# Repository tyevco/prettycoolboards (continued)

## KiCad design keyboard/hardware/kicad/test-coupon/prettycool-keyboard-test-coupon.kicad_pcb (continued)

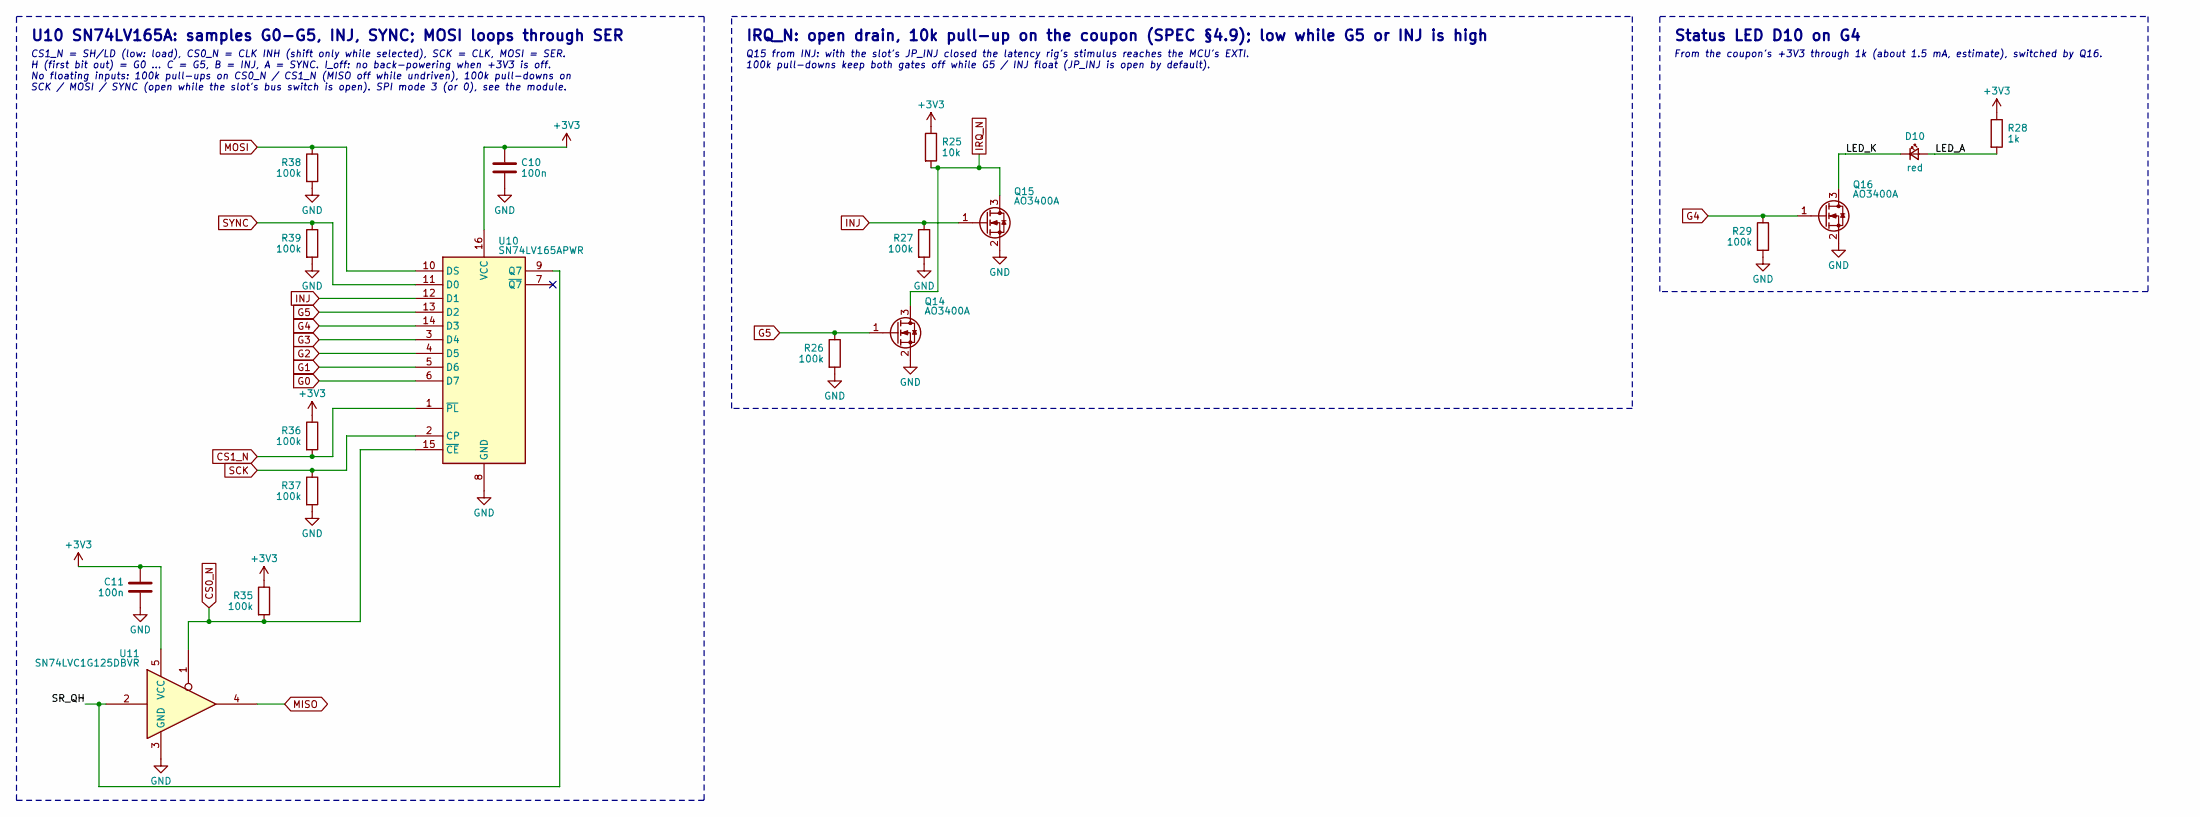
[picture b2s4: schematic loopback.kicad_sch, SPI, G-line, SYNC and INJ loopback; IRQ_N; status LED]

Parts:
C10, C11: 100n; C_0402_1005Metric; MPN CL05B104KO5NNNC; LCSC C1525
D10: red; LED_0603_1608Metric; MPN KT-0603R; LCSC C2286
Q14, Q15, Q16: AO3400A; SOT-23; MPN AO3400A; LCSC C20917
R25: 10k; R_0402_1005Metric; MPN 0402WGF1002TCE; LCSC C25744
R26, R27, R29, R35, R36, R37, R38, R39: 100k; R_0402_1005Metric; MPN 0402WGF1003TCE; LCSC C25741
R28: 1k; R_0402_1005Metric; MPN 0402WGF1001TCE; LCSC C11702
U10: SN74LV165APWR; TSSOP-16_4.4x5mm_P0.65mm; MPN SN74LV165APWR; LCSC C201716
U11: SN74LVC1G125DBVR; SOT-23-5; MPN SN74LVC1G125DBVR; LCSC C23654

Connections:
+3V3: C10.1, C11.1, R25.1, R28.1, R35.1, R36.1, U10.16 (VCC), U11.5 (VCC); also elsewhere on the board
/SPI, G-line, SYNC and INJ loopback; IRQ_N; status LED/LED_A: D10.2 (A), R28.2
/SPI, G-line, SYNC and INJ loopback; IRQ_N; status LED/LED_K: D10.1 (K), Q16.3 (D)
/SPI, G-line, SYNC and INJ loopback; IRQ_N; status LED/SR_QH: U10.9 (Q7), U11.2
CS0_N: R35.2, U10.15 (~CE), U11.1; also elsewhere on the board
CS1_N: R36.2, U10.1 (~PL); also elsewhere on the board
G0: U10.6 (D7); also elsewhere on the board
G1: U10.5 (D6); also elsewhere on the board
G2: U10.4 (D5); also elsewhere on the board
G3: U10.3 (D4); also elsewhere on the board
G4: Q16.1 (G), R29.1, U10.14 (D3); also elsewhere on the board
G5: Q14.1 (G), R26.1, U10.13 (D2); also elsewhere on the board
GND: C10.2, C11.2, Q14.2 (S), Q15.2 (S), Q16.2 (S), R26.2, R27.2, R29.2, R37.2, R38.2, R39.2, U10.8 (GND), U11.3 (GND); also elsewhere on the board
INJ: Q15.1 (G), R27.1, U10.12 (D1); also elsewhere on the board
IRQ_N: Q14.3 (D), Q15.3 (D), R25.2; also elsewhere on the board
MISO: U11.4; also elsewhere on the board
MOSI: R38.1, U10.10 (DS); also elsewhere on the board
SCK: R37.1, U10.2 (CP); also elsewhere on the board
SYNC: R39.1, U10.11 (D0); also elsewhere on the board

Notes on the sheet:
U10 SN74LV165A: samples G0-G5, INJ, SYNC; MOSI loops through SER
CS1_N = SH/LD (low: load), CS0_N = CLK INH (shift only while selected), SCK = CLK, MOSI = SER. H (first bit out) = G0 ... C = G5, B = INJ, A = SYNC. I_off: no back-powering when +3V3 is off. No floating inputs: 100k pull-ups on CS0_N / CS1_N (MISO off while undriven), 100k pull-downs on SCK / MOSI 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
IRQ_N: open drain, 10k pull-up on the coupon (SPEC §4.9); low while G5 or INJ is high
Q15 from INJ: with the slot's JP_INJ closed the latency rig's stimulus reaches the MCU's EXTI. 100k pull-downs keep both gates off while G5 / INJ float (JP_INJ is open by default).
Status LED D10 on G4
From the coupon's +3V3 through 1k (about 1.5 mA, estimate), switched by Q16.

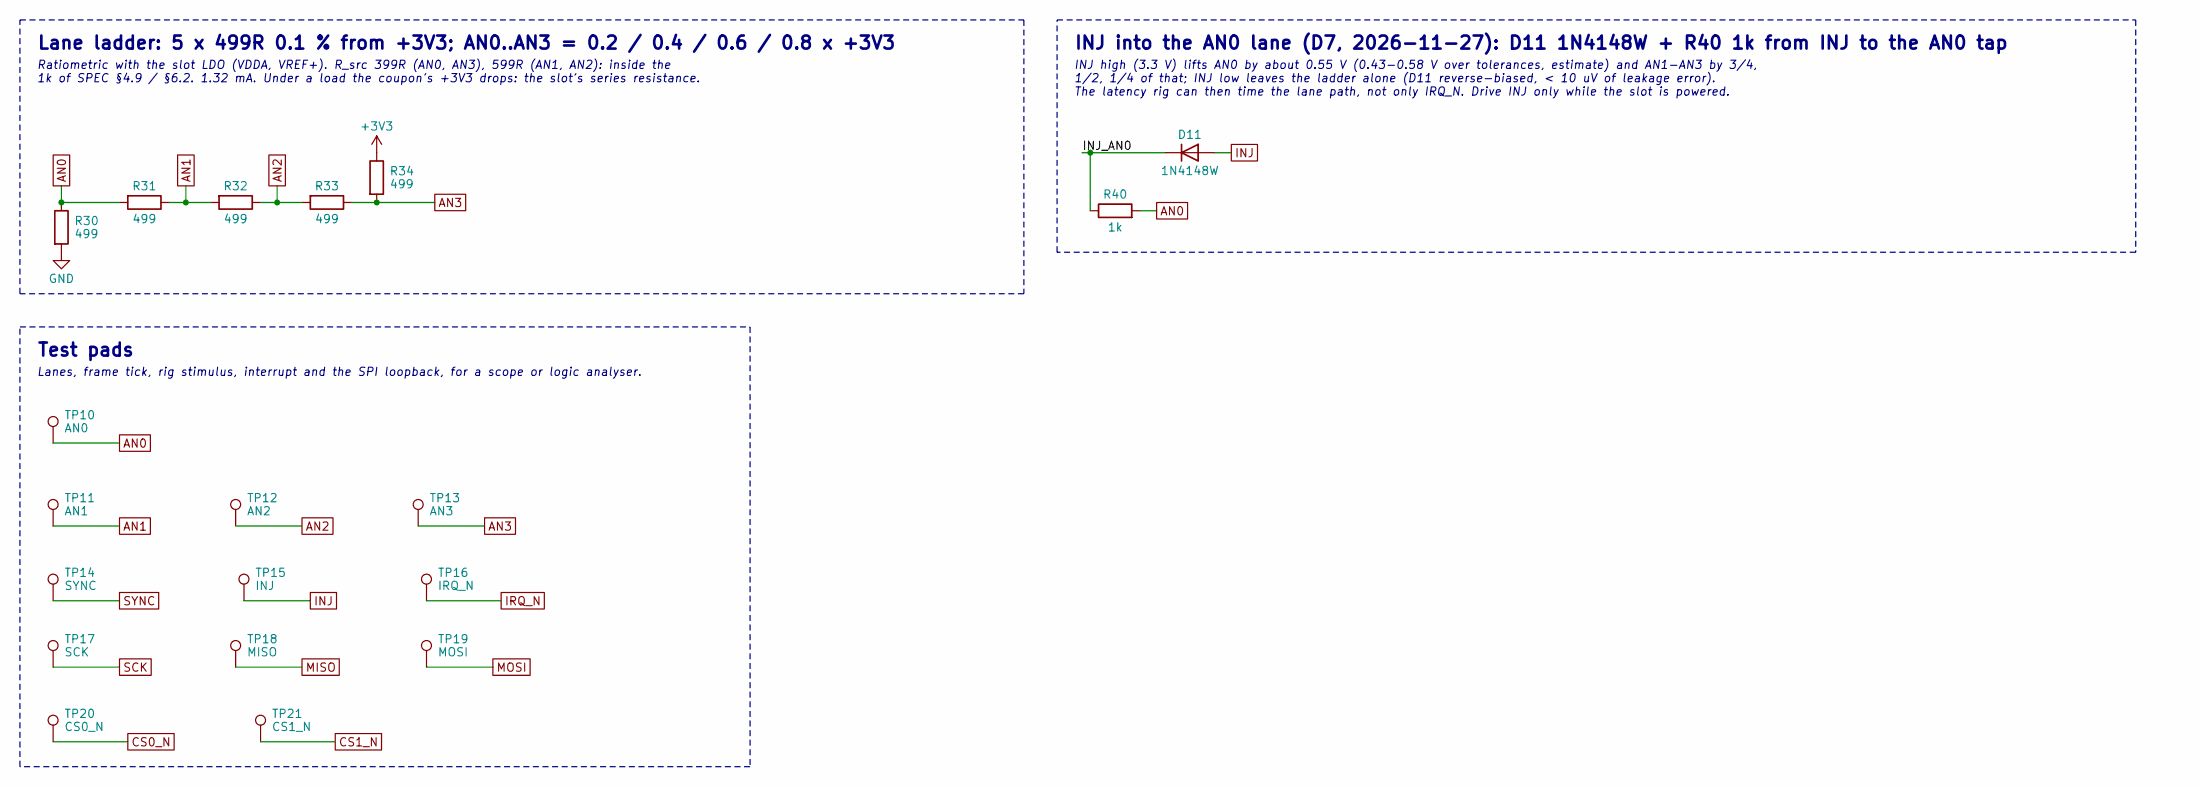
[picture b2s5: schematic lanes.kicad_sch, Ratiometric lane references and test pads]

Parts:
D11: 1N4148W; D_SOD-123; MPN 1N4148W; LCSC C81598
R30, R31, R32, R33, R34: 499; R_0603_1608Metric; MPN AR03BTCX4990; LCSC C2889161
R40: 1k; R_0402_1005Metric; MPN 0402WGF1001TCE; LCSC C11702
TP10: AN0; TestPoint_Pad_D1.0mm
TP11: AN1; TestPoint_Pad_D1.0mm
TP12: AN2; TestPoint_Pad_D1.0mm
TP13: AN3; TestPoint_Pad_D1.0mm
TP14: SYNC; TestPoint_Pad_D1.0mm
TP15: INJ; TestPoint_Pad_D1.0mm
TP16: IRQ_N; TestPoint_Pad_D1.0mm
TP17: SCK; TestPoint_Pad_D1.0mm
TP18: MISO; TestPoint_Pad_D1.0mm
TP19: MOSI; TestPoint_Pad_D1.0mm
TP20: CS0_N; TestPoint_Pad_D1.0mm
TP21: CS1_N; TestPoint_Pad_D1.0mm

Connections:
+3V3: R34.1; also elsewhere on the board
/Ratiometric lane references and test pads/INJ_AN0: D11.1 (K), R40.1
AN0: R30.1, R31.2, R40.2, TP10.1; also elsewhere on the board
AN1: R31.1, R32.2, TP11.1; also elsewhere on the board
AN2: R32.1, R33.2, TP12.1; also elsewhere on the board
AN3: R33.1, R34.2, TP13.1; also elsewhere on the board
CS0_N: TP20.1; also elsewhere on the board
CS1_N: TP21.1; also elsewhere on the board
GND: R30.2; also elsewhere on the board
INJ: D11.2 (A), TP15.1; also elsewhere on the board
IRQ_N: TP16.1; also elsewhere on the board
MISO: TP18.1; also elsewhere on the board
MOSI: TP19.1; also elsewhere on the board
SCK: TP17.1; also elsewhere on the board
SYNC: TP14.1; also elsewhere on the board

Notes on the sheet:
Lane ladder: 5 x 499R 0.1 % from +3V3; AN0..AN3 = 0.2 / 0.4 / 0.6 / 0.8 x +3V3
Ratiometric with the slot LDO (VDDA, VREF+). R_src 399R (AN0, AN3), 599R (AN1, AN2): inside the 1k of SPEC §4.9 / §6.2. 1.32 mA. Under a load the coupon's +3V3 drops: the slot's series resistance.
INJ into the AN0 lane (D7, 2026-11-27): D11 1N4148W + R40 1k from INJ to the AN0 tap
INJ high (3.3 V) lifts AN0 by about 0.55 V (0.43-0.58 V over tolerances, estimate) and AN1-AN3 by 3/4, 1/2, 1/4 of that; INJ low leaves the ladder alone (D11 reverse-biased, < 10 uV of leakage error). The latency rig can then time the lane path, not only IRQ_N. Drive INJ only while the slot is powe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
Test pads
Lanes, frame tick, rig stimulus, interrupt and the SPI loopback, for a scope or logic analyser.

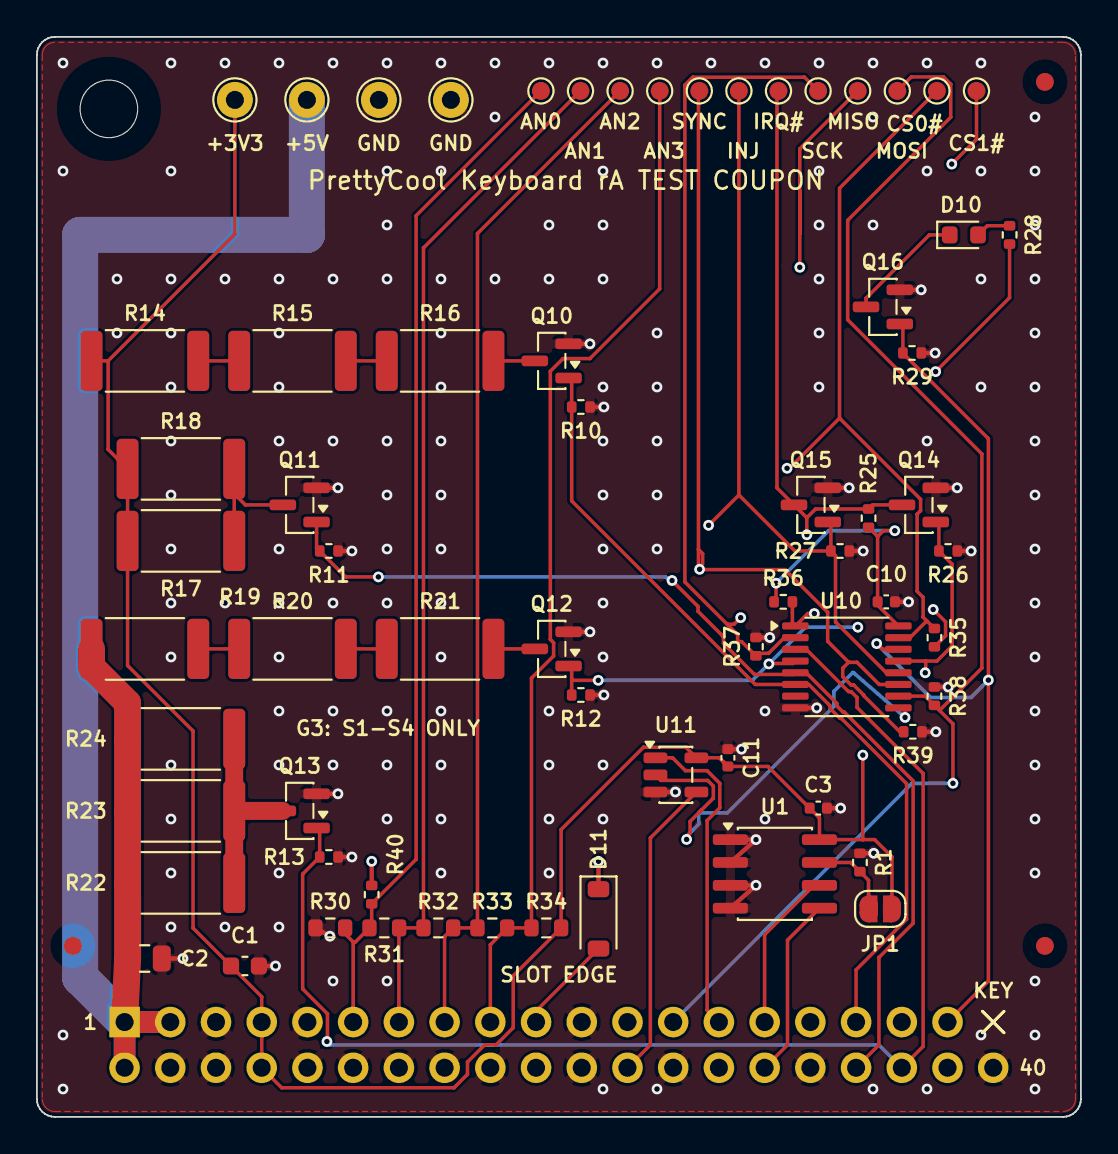
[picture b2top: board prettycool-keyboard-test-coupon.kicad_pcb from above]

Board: 4 copper layers, 58.0 x 60.0 mm, 71 parts (1 on the bottom side), 36 nets.

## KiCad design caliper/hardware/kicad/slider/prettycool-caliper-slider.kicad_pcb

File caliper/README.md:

# PrettyCool Caliper

A 150 mm digital caliper that remembers its readings and sends them wirelessly.

> **Status (2026-11-10): rev A designed, not built.** Schematics captured (ERC clean, 2 waived); both boards laid
> out and routed (KiCad 10.0.8 DRC + schematic parity: 0 errors, 0 unconnected); both fab packages pass
> `release.py`, including the jlcplace placement gate (slider 107 rows, 0 red, 0 yellow); the mechanics pass the clash
> check against the routed board; the firmware builds for the ESP32-S3 and passes its host tests. Nothing has been
> fabricated, flashed, printed or measured, and no SPICE simulation has been run. Every figure here is a design
> target until the prototype passes [bring-up](docs/bringup.md).

| | |
|---|---|
| Sensing | AS5311 magnetic linear encoder over 2 mm-pole tape (0.488 µm internal resolution: the 1.95 µm quadrature count interpolated with the 12-bit SSI position), plus an experimental 8-phase capacitive scale on its own PCB, read side by side |
| Brains | ESP32-S3-MINI-1: BLE 5 and Wi-Fi |
| Display | 1.14 in colour IPS, landscape: big reading, live graph, go/no-go gauge, stats |
| Wireless | BLE HID keyboard (types the reading into any spreadsheet), a companion GATT app, a Wi-Fi web page, MQTT/HTTP push |
| Memory | Thousands of readings with timestamps and tolerance profiles; CSV export over USB, Wi-Fi or BLE |
| Smarts | Tolerance / go-no-go, min/max/mean/σ stats, 6-axis IMU (accelerometer + gyroscope): wake-on-pickup, auto-hold, orientation tracking; a compass (IIS2MDC magnetometer) as a reference that keeps the relative yaw from drifting: beside a steel beam it reads the local field, not north, and how well that works is unmeasured |
| Power | 135 mAh LiPo (501230 class, behind the board), USB-C charging (BQ25180), fuel gauge, buck-boost 3V3. Estimated ≈ 3 days per charge on a typical shop day (30 min measuring a day), ≈ 1 h 40 min of continuous measuring ([architecture §5](docs/architecture.md)); not measured |
| Body | Rev A: printed slider on a ground 20 × 4 mm flat-stock beam. Rev B: CNC-machined drawings. Slider housing 77 × 39 × 16 mm (slimmed from 77 × 52 × 16 on 2026-11-09) |

**[3D gallery](https://tyevco.github.io/prettycoolboards/caliper/gallery/):** rotate the assembly, the exploded
view, the housing on its own, the before/after slim-down and both circuit boards, plus the full render set.

## Documentation

| Document | Contents |
|---|---|
| [docs/architecture.md](docs/architecture.md) | System overview, decisions and the alternatives that were rejected, power budget |
| [hardware/design/SPEC.md](hardware/design/SPEC.md) | **Architecture of record**: boards, placement, power tree, pin map |
| [docs/electronics.md](docs/electronics.md) | Schematics, boards, ERC/DRC status, renders |
| [docs/mechanical.md](docs/mechanical.md) | Beam, slider housing, gibs, jaws; printed rev A and machined rev B |
| [docs/simulation.md](docs/simulation.md) | Placeholder: the SPICE checks of the power path and the capacitive front-end are not written or run yet |
| [docs/firmware.md](docs/firmware.md) | ESP-IDF firmware: sensing, UI, BLE, Wi-Fi, storage, power |
| [docs/app.md](docs/app.md) | Web Bluetooth companion page |
| [docs/assembly.md](docs/assembly.md) | Ordering (JLCPCB), sourcing, assembly |
| [docs/ordering.md](docs/ordering.md) | One-page order checklist: JLC options, panel, rough cost, off-board parts (prepared, nothing ordered) |
| [docs/bringup.md](docs/bringup.md) | The bring-up procedure B-0…B-17: test pads, supplies, meter points, expected values, the `bu` console checks; written, not run |

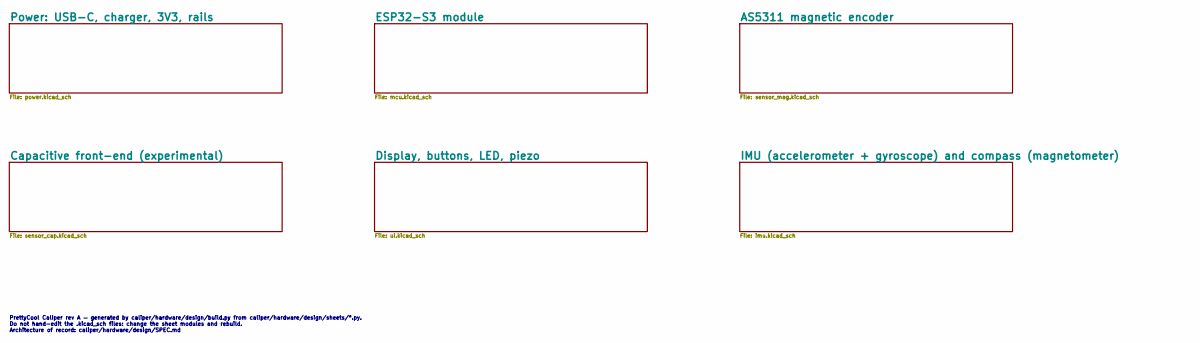
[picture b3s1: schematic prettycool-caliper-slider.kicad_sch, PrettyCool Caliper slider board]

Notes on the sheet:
PrettyCool Caliper rev A — generated by caliper/hardware/design/build.py from caliper/hardware/design/sheets/*.py. Do not hand-edit the .kicad_sch files: change the sheet modules and rebuild. Architecture of record: caliper/hardware/design/SPEC.md

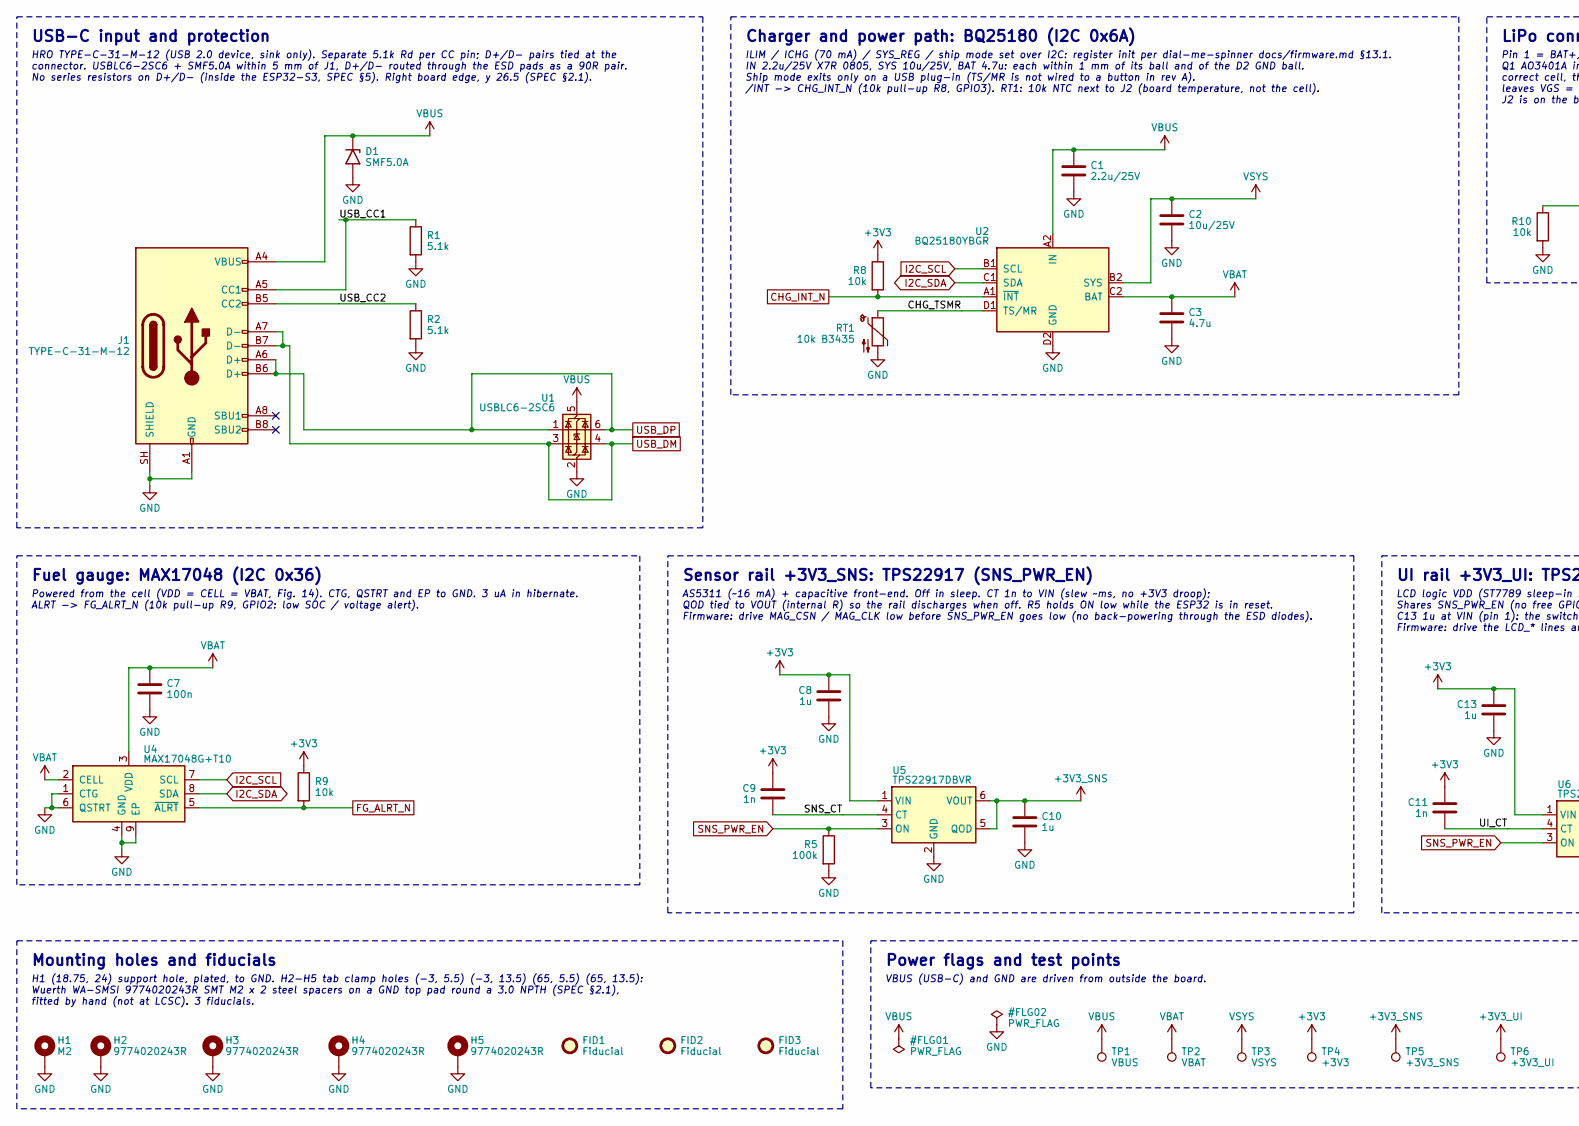
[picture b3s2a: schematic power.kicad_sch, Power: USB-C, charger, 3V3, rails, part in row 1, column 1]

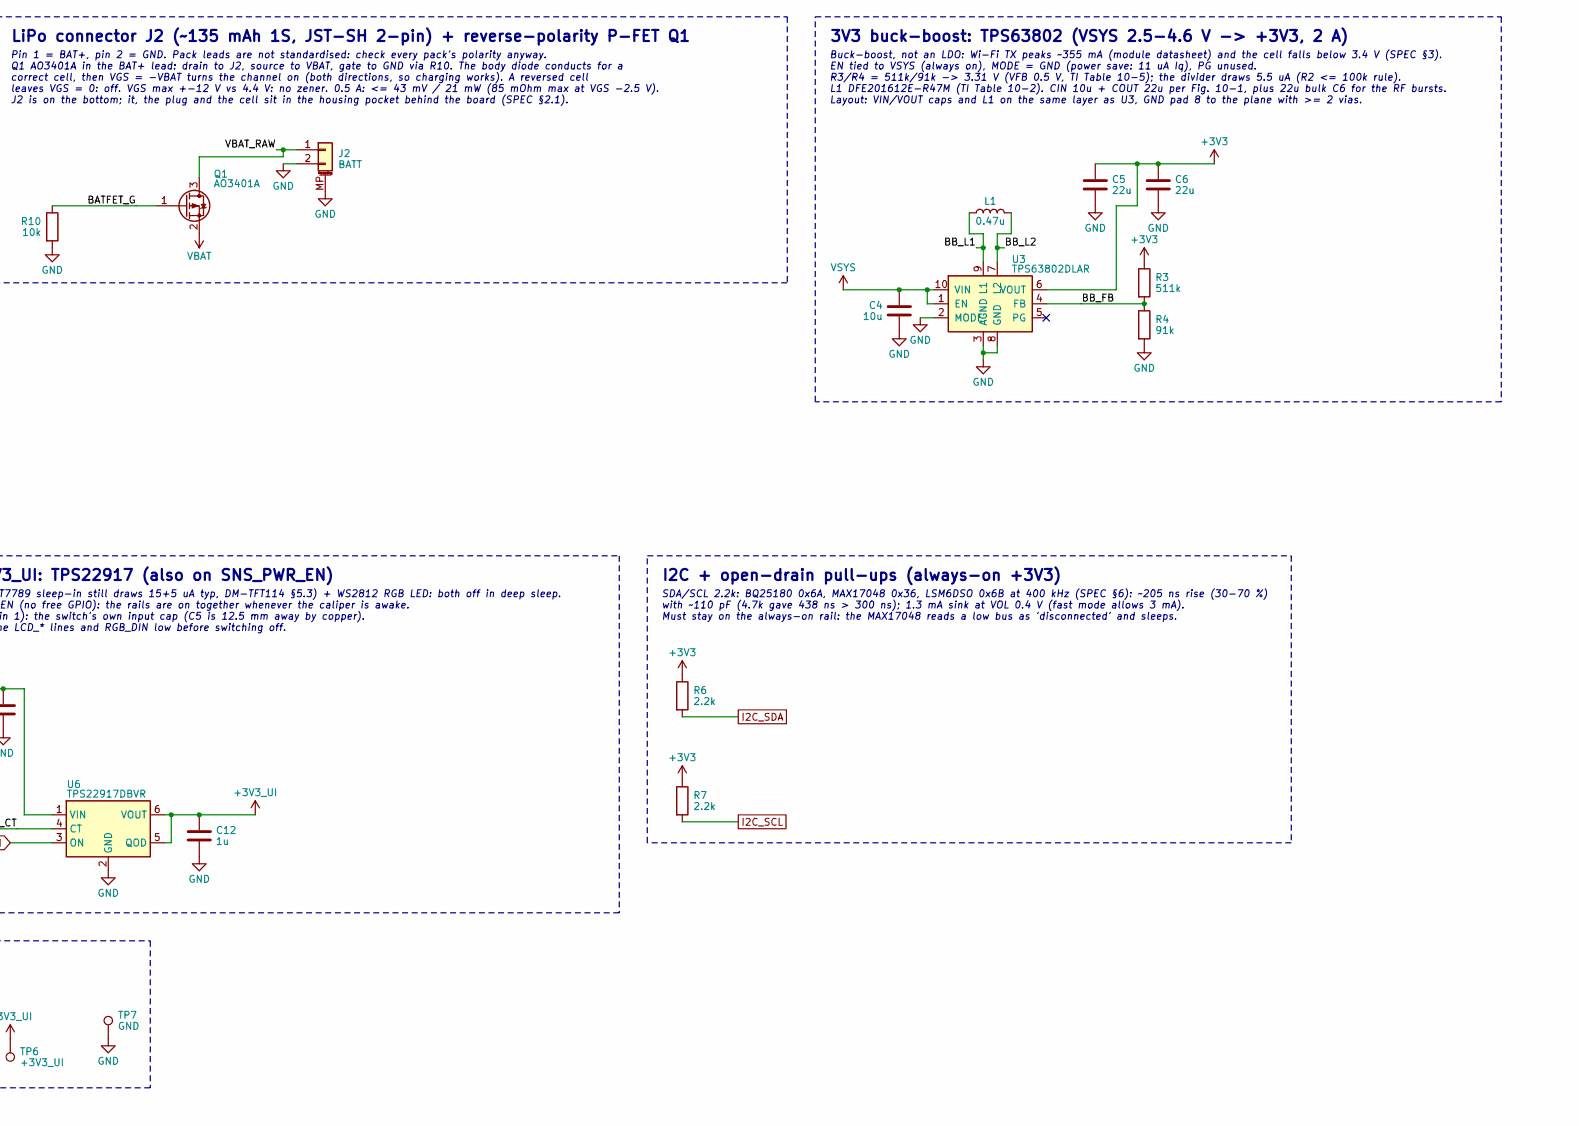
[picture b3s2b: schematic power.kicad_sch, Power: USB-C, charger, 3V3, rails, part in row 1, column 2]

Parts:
C1: 2.2u/25V; C_0805_2012Metric; MPN CC0805KKX7R8BB225; LCSC C277470
C2: 10u/25V; C_0603_1608Metric; MPN CL10A106MA8NRNC; LCSC C96446
C3: 4.7u; C_0603_1608Metric; MPN CL10A475KO8NNNC; LCSC C19666
C4: 10u; C_0603_1608Metric; MPN CL10A106KP8NNNC; LCSC C19702
C5, C6: 22u; C_0603_1608Metric; MPN CL10A226MQ8NRNC; LCSC C59461
C7: 100n; C_0402_1005Metric; MPN CL05B104KO5NNNC; LCSC C1525
C8, C10, C12, C13: 1u; C_0402_1005Metric; MPN CL05A105KA5NQNC; LCSC C52923
C9, C11: 1n; C_0402_1005Metric; MPN 0402B102K500NT; LCSC C1523
D1: SMF5.0A; D_SMF; MPN SMF5.0A; LCSC C151296
FID1, FID2, FID3: Fiducial; Fiducial_1mm_Mask2mm
H1: M2; MountingHole_2.2mm_M2_Pad_Via
H2, H3, H4, H5: 9774020243R; Wuerth_WA-SMSI-M2_H2mm_9774020243_Pullback
J1: TYPE-C-31-M-12; USB_C_Receptacle_HRO_TYPE-C-31-M-12; MPN TYPE-C-31-M-12; LCSC C165948
J2: BATT; JST_SH_SM02B-SRSS-TB_1x02-1MP_P1.00mm_Horizontal; MPN SM02B-SRSS-TB(LF)(SN); LCSC C160402
L1: 0.47u; L_Murata_DFE201610P; MPN DFE201612E-R47M=P2; LCSC C668312
Q1: AO3401A; SOT-23; MPN AO3401A; LCSC C15127
R1, R2: 5.1k; R_0402_1005Metric; MPN 0402WGF5101TCE; LCSC C25905
R3: 511k; R_0402_1005Metric; MPN 0402WGF5113TCE; LCSC C64042
R4: 91k; R_0402_1005Metric; MPN 0402WGF9102TCE; LCSC C4147
R5: 100k; R_0402_1005Metric; MPN 0402WGF1003TCE; LCSC C25741
R6, R7: 2.2k; R_0402_1005Metric; MPN 0402WGF2201TCE; LCSC C25879
R8, R9, R10: 10k; R_0402_1005Metric; MPN 0402WGF1002TCE; LCSC C25744
RT1: 10k B3435; R_0402_1005Metric; MPN NCP15XH103F03RC; LCSC C77131
TP1: VBUS; TestPoint_Pad_D1.0mm
TP2: VBAT; TestPoint_Pad_D1.0mm
TP3: VSYS; TestPoint_Pad_D1.0mm
TP4: +3V3; TestPoint_Pad_D1.0mm
TP5: +3V3_SNS; TestPoint_Pad_D1.0mm
TP6: +3V3_UI; TestPoint_Pad_D1.0mm
TP7: GND; TestPoint_Pad_D1.0mm
U1: USBLC6-2SC6; SOT-23-6; MPN USBLC6-2SC6; LCSC C7519
U2: BQ25180YBGR; Texas_DSBGA-8_1.04x1.59mm_Layout2x4_P0.4mm_YBG0008; MPN BQ25180YBGR; LCSC C3682423
U3: TPS63802DLAR; Texas_DLA0010A_VSON-HR-10_2x3mm_P0.5mm; MPN TPS63802DLAR; LCSC C2845237
U4: MAX17048G+T10; TDFN-8-1EP_2x2mm_P0.5mm_EP0.8x1.2mm; MPN MAX17048G+T10; LCSC C2682616
U5, U6: TPS22917DBVR; SOT-23-6; MPN TPS22917DBVR; LCSC C2681320

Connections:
+3V3: C5.1, C6.1, C8.1, C9.2, C11.2, C13.1, R3.1, R6.1, R7.1, R8.1, R9.1, TP4.1, U3.6 (VOUT), U5.1 (VIN), U6.1 (VIN); also elsewhere on the board
+3V3_SNS: C10.1, TP5.1, U5.5 (QOD), U5.6 (VOUT); also elsewhere on the board
+3V3_UI: C12.1, TP6.1, U6.5 (QOD), U6.6 (VOUT); also elsewhere on the board
/Power: USB-C, charger, 3V3, rails/BATFET_G: Q1.1 (G), R10.1
/Power: USB-C, charger, 3V3, rails/BB_FB: R3.2, R4.1, U3.4 (FB)
/Power: USB-C, charger, 3V3, rails/BB_L1: L1.1, U3.9 (L1)
/Power: USB-C, charger, 3V3, rails/BB_L2: L1.2, U3.7 (L2)
/Power: USB-C, charger, 3V3, rails/CHG_TSMR: RT1.1, U2.D1 (TS/MR)
/Power: USB-C, charger, 3V3, rails/SNS_CT: C9.1, U5.4 (CT)
/Power: USB-C, charger, 3V3, rails/UI_CT: C11.1, U6.4 (CT)
/Power: USB-C, charger, 3V3, rails/USB_CC1: J1.A5 (CC1), R1.1
/Power: USB-C, charger, 3V3, rails/USB_CC2: J1.B5 (CC2), R2.1
/Power: USB-C, charger, 3V3, rails/VBAT_RAW: J2.1, Q1.3 (D)
CHG_INT_N: R8.2, U2.A1 (~INT); also elsewhere on the board
FG_ALRT_N: R9.2, U4.5 (~ALRT); also elsewhere on the board
GND: C1.2, C2.2, C3.2, C4.2, C5.2, C6.2, C7.2, C8.2, C10.2, C12.2, C13.2, D1.2 (A2), H1.1, H2.1, H3.1, H4.1, H5.1, J1.A1 (GND), J1.A12 (GND), J1.B1 (GND), J1.B12 (GND), J1.SH (SHIELD), J2.2, J2.MP (MountPin), R1.2, R2.2, R4.2, R5.2, R10.2, RT1.2, TP7.1, U1.2 (GND), U2.D2 (GND), U3.2 (MODE), U3.3 (AGND), U3.8 (GND), U4.1 (CTG), U4.4 (GND), U4.6 (QSTRT), U4.9 (EP), U5.2 (GND), U6.2 (GND); also elsewhere on the board
I2C_SCL: R7.2, U2.B1 (SCL), U4.7 (SCL); also elsewhere on the board
I2C_SDA: R6.2, U2.C1 (SDA), U4.8 (SDA); also elsewhere on the board
SNS_PWR_EN: R5.1, U5.3 (ON), U6.3 (ON); also elsewhere on the board
USB_DM: J1.A7 (D-), J1.B7 (D-), U1.3 (I/O2), U1.4 (I/O2); also elsewhere on the board
USB_DP: J1.A6 (D+), J1.B6 (D+), U1.1 (I/O1), U1.6 (I/O1); also elsewhere on the board
VBAT: C3.1, C7.1, Q1.2 (S), TP2.1, U2.C2 (BAT), U4.2 (CELL), U4.3 (VDD)
VBUS: C1.1, D1.1 (A1), J1.A4 (VBUS), J1.A9 (VBUS), J1.B4 (VBUS), J1.B9 (VBUS), TP1.1, U1.5 (VBUS), U2.A2 (IN)
VSYS: C2.1, C4.1, TP3.1, U2.B2 (SYS), U3.1 (EN), U3.10 (VIN)

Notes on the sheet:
USB-C input and protection
HRO TYPE-C-31-M-12 (USB 2.0 device, sink only). Separate 5.1k Rd per CC pin; D+/D- pairs tied at the connector. USBLC6-2SC6 + SMF5.0A within 5 mm of J1, D+/D- routed through the ESD pads as a 90R pair. No series resistors on D+/D- (inside the ESP32-S3, SPEC §5). Right board edge, y 26.5 (SPEC §2.1).
Charger and power path: BQ25180 (I2C 0x6A)
ILIM / ICHG (70 mA) / SYS_REG / ship mode set over I2C: register init per dial-me-spinner docs/firmware.md §13.1. IN 2.2u/25V X7R 0805, SYS 10u/25V, BAT 4.7u: each within 1 mm of its ball and of the D2 GND ball. Ship mode exits only on a USB plug-in (TS/MR is not wired to a button in rev A). /INT -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
LiPo connector J2 (~135 mAh 1S, JST-SH 2-pin) + reverse-polarity P-FET Q1
Pin 1 = BAT+, pin 2 = GND. Pack leads are not standardised: check every pack's polarity anyway. Q1 AO3401A in the BAT+ lead: drain to J2, source to VBAT, gate to GND via R10. The body diode conducts for a correct cell, then VGS = -VBAT turns the channel on (both directions, so charging works). A re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
3V3 buck-boost: TPS63802 (VSYS 2.5-4.6 V -> +3V3, 2 A)
Buck-boost, not an LDO: Wi-Fi TX peaks ~355 mA (module datasheet) and the cell falls below 3.4 V (SPEC §3). EN tied to VSYS (always on), MODE = GND (power save: 11 uA Iq), PG unused. R3/R4 = 511k/91k -> 3.31 V (VFB 0.5 V, TI Table 10-5); the divider draws 5.5 uA (R2 <= 100k rule). L1 DFE201612E-R47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
Fuel gauge: MAX17048 (I2C 0x36)
Powered from the cell (VDD = CELL = VBAT, Fig. 14). CTG, QSTRT and EP to GND. 3 uA in hibernate. ALRT -> FG_ALRT_N (10k pull-up R9, GPIO2: low SOC / voltage alert).
Sensor rail +3V3_SNS: TPS22917 (SNS_PWR_EN)
AS5311 (~16 mA) + capacitive front-end. Off in sleep. CT 1n to VIN (slew ~ms, no +3V3 droop); QOD tied to VOUT (internal R) so the rail discharges when off. R5 holds ON low while the ESP32 is in reset. Firmware: drive MAG_CSN / MAG_CLK low before SNS_PWR_EN goes low (no back-powering through the ES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
UI rail +3V3_UI: TPS22917 (also on SNS_PWR_EN)
LCD logic VDD (ST7789 sleep-in still draws 15+5 uA typ, DM-TFT114 §5.3) + WS2812 RGB LED: both off in deep sleep. Shares SNS_PWR_EN (no free GPIO): the rails are on together whenever the caliper is awake. C13 1u at VIN (pin 1): the switch's own input cap (C5 is 12.5 mm away by copper). Firmware: dr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
I2C + open-drain pull-ups (always-on +3V3)
SDA/SCL 2.2k: BQ25180 0x6A, MAX17048 0x36, LSM6DSO 0x6B at 400 kHz (SPEC §6): ~205 ns rise (30-70 %) with ~110 pF (4.7k gave 438 ns > 300 ns); 1.3 mA sink at VOL 0.4 V (fast mode allows 3 mA). Must stay on the always-on rail: the MAX17048 reads a low bus as 'disconnected' and sleeps.
Mounting holes and fiducials
H1 (18.75, 24) support hole, plated, to GND. H2-H5 tab clamp holes (-3, 5.5) (-3, 13.5) (65, 5.5) (65, 13.5): Wuerth WA-SMSI 9774020243R SMT M2 x 2 steel spacers on a GND top pad round a 3.0 NPTH (SPEC §2.1), fitted by hand (not at LCSC). 3 fiducials.
Power flags and test points
VBUS (USB-C) and GND are driven from outside the board.

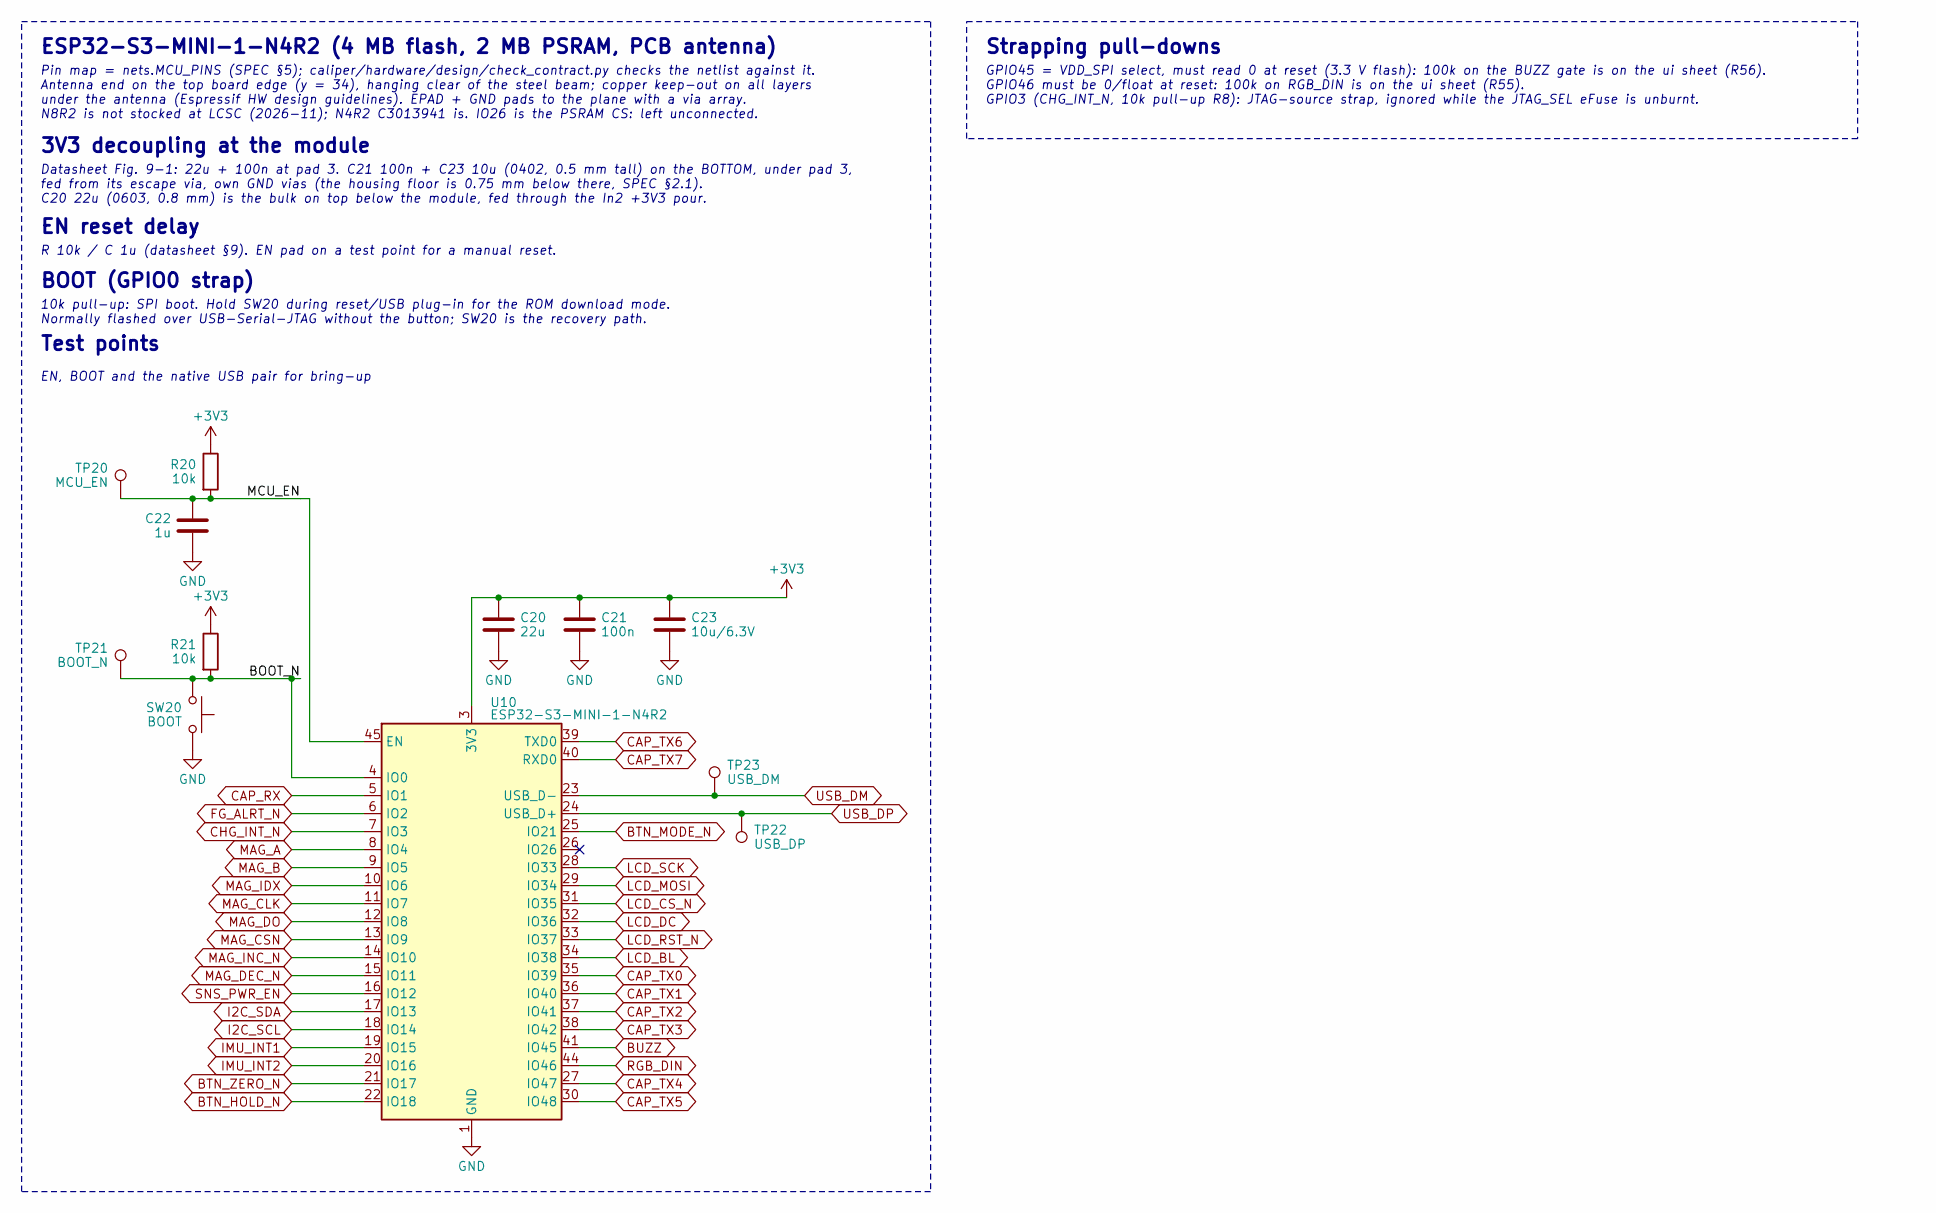
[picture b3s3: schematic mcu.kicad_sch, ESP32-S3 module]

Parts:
C20: 22u; C_0603_1608Metric; MPN CL10A226MQ8NRNC; LCSC C59461
C21: 100n; C_0402_1005Metric; MPN CL05B104KO5NNNC; LCSC C1525
C22: 1u; C_0402_1005Metric; MPN CL05A105KA5NQNC; LCSC C52923
C23: 10u/6.3V; C_0402_1005Metric; MPN CL05A106MQ5NUNC; LCSC C15525
R20, R21: 10k; R_0402_1005Metric; MPN 0402WGF1002TCE; LCSC C25744
SW20: BOOT; SW_SPST_TS-1088-xR020; MPN TS-1088-AR02016; LCSC C720477
TP20: MCU_EN; TestPoint_Pad_D1.0mm
TP21: BOOT_N; TestPoint_Pad_D1.0mm
TP22: USB_DP; TestPoint_Pad_D1.0mm
TP23: USB_DM; TestPoint_Pad_D1.0mm
U10: ESP32-S3-MINI-1-N4R2; ESP32-S2-MINI-1; MPN ESP32-S3-MINI-1-N4R2; LCSC C3013941

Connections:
+3V3: C20.1, C21.1, C23.1, R20.1, R21.1, U10.3 (3V3); also elsewhere on the board
/ESP32-S3 module/BOOT_N: R21.2, SW20.1, TP21.1, U10.4 (IO0)
/ESP32-S3 module/MCU_EN: C22.1, R20.2, TP20.1, U10.45 (EN)
BTN_HOLD_N: U10.22 (IO18); also elsewhere on the board
BTN_MODE_N: U10.25 (IO21); also elsewhere on the board
BTN_ZERO_N: U10.21 (IO17); also elsewhere on the board
BUZZ: U10.41 (IO45); also elsewhere on the board
CAP_RX: U10.5 (IO1); also elsewhere on the board
CAP_TX0: U10.35 (IO39); also elsewhere on the board
CAP_TX1: U10.36 (IO40); also elsewhere on the board
CAP_TX2: U10.37 (IO41); also elsewhere on the board
CAP_TX3: U10.38 (IO42); also elsewhere on the board
CAP_TX4: U10.27 (IO47); also elsewhere on the board
CAP_TX5: U10.30 (IO48); also elsewhere on the board
CAP_TX6: U10.39 (TXD0); also elsewhere on the board
CAP_TX7: U10.40 (RXD0); also elsewhere on the board
CHG_INT_N: U10.7 (IO3); also elsewhere on the board
FG_ALRT_N: U10.6 (IO2); also elsewhere on the board
GND: C20.2, C21.2, C22.2, C23.2, SW20.2, U10.1 (GND), U10.2 (GND), U10.42 (GND), U10.43 (GND), U10.46 (GND), U10.47 (GND), U10.48 (GND), U10.49 (GND), U10.50 (GND), U10.51 (GND), U10.52 (GND), U10.53 (GND), U10.54 (GND), U10.55 (GND), U10.56 (GND), U10.57 (GND), U10.58 (GND), U10.59 (GND), U10.60 (GND), U10.61 (GND), U10.62 (GND), U10.63 (GND), U10.64 (GND), U10.65 (GND); also elsewhere on the board
I2C_SCL: U10.18 (IO14); also elsewhere on the board
I2C_SDA: U10.17 (IO13); also elsewhere on the board
IMU_INT1: U10.19 (IO15); also elsewhere on the board
IMU_INT2: U10.20 (IO16); also elsewhere on the board
LCD_BL: U10.34 (IO38); also elsewhere on the board
LCD_CS_N: U10.31 (IO35); also elsewhere on the board
LCD_DC: U10.32 (IO36); also elsewhere on the board
LCD_MOSI: U10.29 (IO34); also elsewhere on the board
LCD_RST_N: U10.33 (IO37); also elsewhere on the board
LCD_SCK: U10.28 (IO33); also elsewhere on the board
MAG_A: U10.8 (IO4); also elsewhere on the board
MAG_B: U10.9 (IO5); also elsewhere on the board
MAG_CLK: U10.11 (IO7); also elsewhere on the board
MAG_CSN: U10.13 (IO9); also elsewhere on the board
MAG_DEC_N: U10.15 (IO11); also elsewhere on the board
MAG_DO: U10.12 (IO8); also elsewhere on the board
MAG_IDX: U10.10 (IO6); also elsewhere on the board
MAG_INC_N: U10.14 (IO10); also elsewhere on the board
RGB_DIN: U10.44 (IO46); also elsewhere on the board
SNS_PWR_EN: U10.16 (IO12); also elsewhere on the board
USB_DM: TP23.1, U10.23 (USB_D-); also elsewhere on the board
USB_DP: TP22.1, U10.24 (USB_D+); also elsewhere on the board

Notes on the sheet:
ESP32-S3-MINI-1-N4R2 (4 MB flash, 2 MB PSRAM, PCB antenna)
Pin map = nets.MCU_PINS (SPEC §5); caliper/hardware/design/check_contract.py checks the netlist against it. Antenna end on the top board edge (y = 34), hanging clear of the steel beam; copper keep-out on all layers under the antenna (Espressif HW design guidelines). EPAD + GND pads to the plane wit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
3V3 decoupling at the module
Datasheet Fig. 9-1: 22u + 100n at pad 3. C21 100n + C23 10u (0402, 0.5 mm tall) on the BOTTOM, under pad 3, fed from its escape via, own GND vias (the housing floor is 0.75 mm below there, SPEC §2.1). C20 22u (0603, 0.8 mm) is the bulk on top below the module, fed through the In2 +3V3 pour.
EN reset delay
R 10k / C 1u (datasheet §9). EN pad on a test point for a manual reset.
BOOT (GPIO0 strap)
10k pull-up: SPI boot. Hold SW20 during reset/USB plug-in for the ROM download mode. Normally flashed over USB-Serial-JTAG without the button; SW20 is the recovery path.
Test points
EN, BOOT and the native USB pair for bring-up
Strapping pull-downs
GPIO45 = VDD_SPI select, must read 0 at reset (3.3 V flash): 100k on the BUZZ gate is on the ui sheet (R56). GPIO46 must be 0/float at reset: 100k on RGB_DIN is on the ui sheet (R55). GPIO3 (CHG_INT_N, 10k pull-up R8): JTAG-source strap, ignored while the JTAG_SEL eFuse is unburnt.
